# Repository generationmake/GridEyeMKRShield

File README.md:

# GridEyeMKRShield
Shield with Panasonic Grid-Eye Infrared Sensor for Arduino MKR

## PCB

### Top

### Bottom

## Resources

### Datasheets

 * tbd
 
### Arduino Libraries

 * tbd

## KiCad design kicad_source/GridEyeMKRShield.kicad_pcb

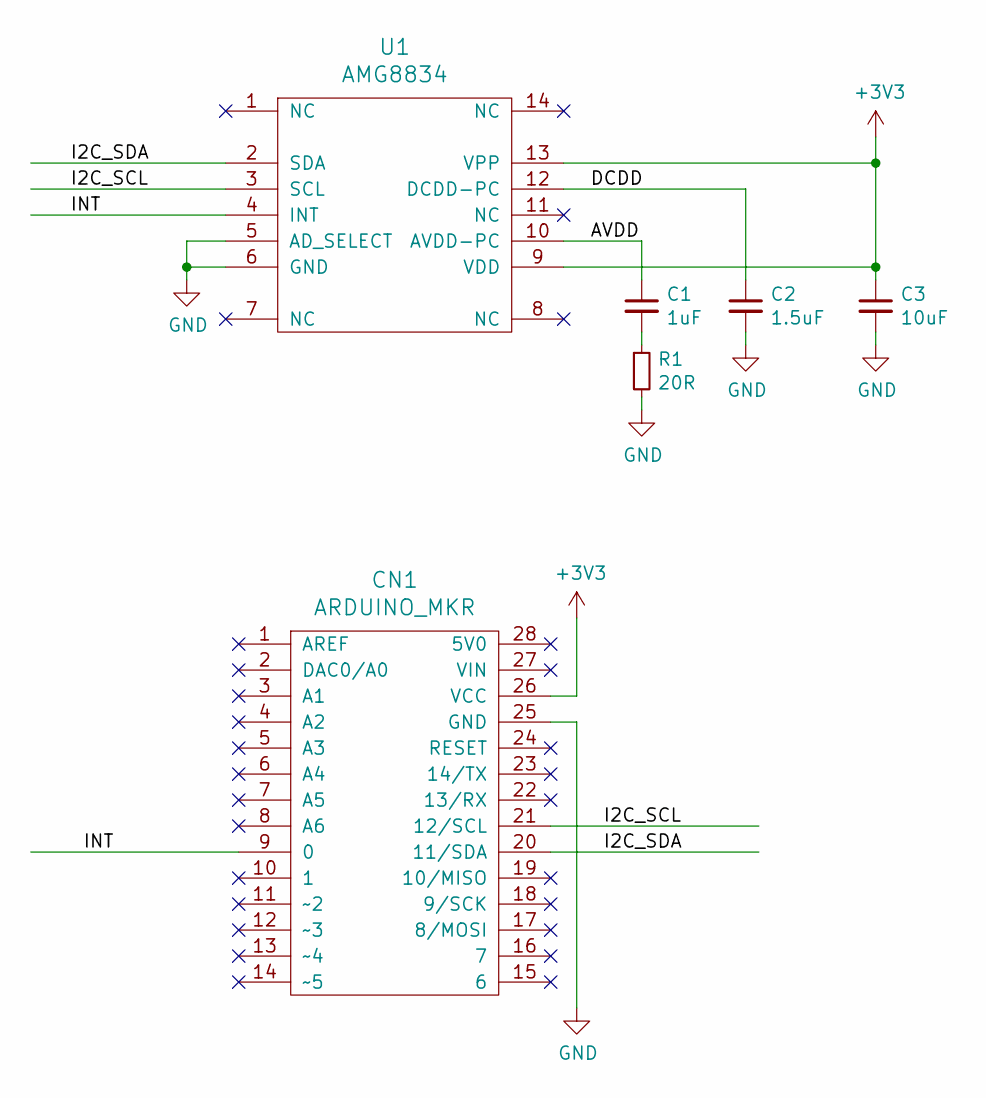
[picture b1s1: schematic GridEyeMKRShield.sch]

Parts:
C1: 1uF; C_0603
C2: 1.5uF; C_0603
C3: 10uF; C_0603
CN1: ARDUINO_MKR
R1: 20R; R_0603
U1: AMG8834; AMG88xx

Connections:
+3V3: C3.1, CN1.26 (VCC), U1.9 (VDD), U1.13 (VPP)
/AVDD: C1.1, U1.10 (AVDD-PC)
/DCDD: C2.1, U1.12 (DCDD-PC)
/I2C_SCL: CN1.21 (12/SCL), U1.3 (SCL)
/I2C_SDA: CN1.20 (11/SDA), U1.2 (SDA)
/INT: CN1.9 (0), U1.4 (INT)
GND: C2.2, C3.2, CN1.25 (GND), R1.2, U1.5 (AD_SELECT), U1.6 (GND)
unnamed: C1.2, R1.1

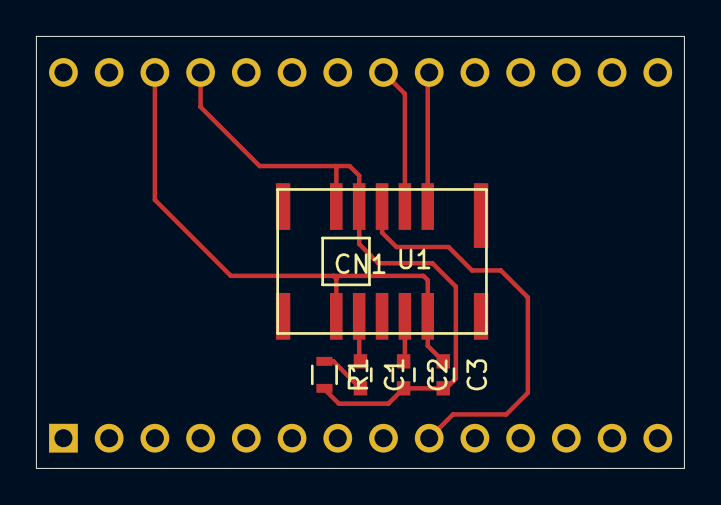
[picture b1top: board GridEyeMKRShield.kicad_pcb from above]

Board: 2 copper layers, 36.0 x 24.0 mm, 6 parts (0 on the bottom side), 8 nets.

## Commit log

2020-11-15 added readme
2020-11-15 added kicad project
2020-11-15 added schematic pdf and image
